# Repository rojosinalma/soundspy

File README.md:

<h1 align="center">soundspy</h1>
<p align="center">Real-time multi-node sound monitoring system for ESP32</p>

<p align="center">

</p>

ESP32 nodes with I2S MEMS microphones sample audio, meter it in six frequency bands plus an overall level, and publish the readings over MQTT. The dashboard discovers the nodes, shows live meters, spectrum and an hour of history per node, relays live audio from any node to the browser, and sends alerts (Telegram, Discord, ntfy, Pushover, email) when a configurable rule fires. One application is keeping an eye on how much of a rehearsal or a mix makes it through a shared wall; the same setup works for any room you want to listen to from elsewhere.

Hardware, firmware, dashboard, enclosure and design notes are documented in [`docs/`](docs/).

## Requirements

**Dashboard**
- Docker 24+ with Docker Compose v2 (or Python 3.12+ to run from source)
- An MQTT broker reachable by both the dashboard and the nodes, for example Eclipse Mosquitto 2.x

**Firmware**
- arduino-cli 1.x with the `esp32:esp32` core 3.3+
- The Esp32Base library for the current firmware (`firmware/`); the legacy firmware (`node_firmware/`) builds with PubSubClient, WebSockets and ArduinoJson from the library index

**Hardware (per node)**
- ESP32 development board (38-pin DevKit with 4 MB flash)
- ICS-43434 or INMP441 I2S MEMS microphone, optionally on the carrier PCB in `pcb/` — wiring in [docs/hardware.md](docs/hardware.md)

## Installation

```bash
git clone https://github.com/rojosinalma/soundspy.git && cd soundspy
cp .env.example .env     # broker address and credentials, dashboard port
docker compose up -d     # pulls ghcr.io/rojosinalma/soundspy:latest
```

The image runs as uid 1000; make sure `./data` is writable by that user (`chown -R 1000:1000 data`).

Then build and flash a node:

```bash
./scripts/init_arduino.sh                                     # ESP32 core + libraries (once)
ESP32_BASE_DIR=/path/to/Esp32Base ./scripts/build_firmware.sh
```

Flash `builds/soundspy_latest.bin` over USB the first time, then join the node's WiFi setup portal and enter your network and broker settings. Flashing, OTA updates and the legacy firmware are covered in [docs/firmware.md](docs/firmware.md).

## Usage

Open `http://<host>:8091`. A node appears on the dashboard as soon as it publishes; click its name to rename it, drag the threshold marker to set its alert level, and use the gain, sleep and live-audio controls on the card. Notification channels and alert rules live under **Settings**. The HTTP API (`GET /api/nodes`, `POST /api/control`, `GET /health`, …) is listed in [docs/dashboard.md](docs/dashboard.md).

## Development

```bash
# dashboard from source (templates reload; restart for Python changes)
cd dashboard && pip install -r requirements.txt && MQTT_HOST=<broker> DB_PATH=./soundspy.db python app.py

# checks
python -m py_compile dashboard/*.py && bash -n scripts/*.sh
./scripts/build_firmware.sh legacy
```

Layout, the Docker dev loop, enclosure rendering and the release flow are in [docs/development.md](docs/development.md); contribution rules in [CONTRIBUTING.md](CONTRIBUTING.md).

## License

[AGPL-3.0](LICENSE) — Copyright (C) 2026 rojosinalma

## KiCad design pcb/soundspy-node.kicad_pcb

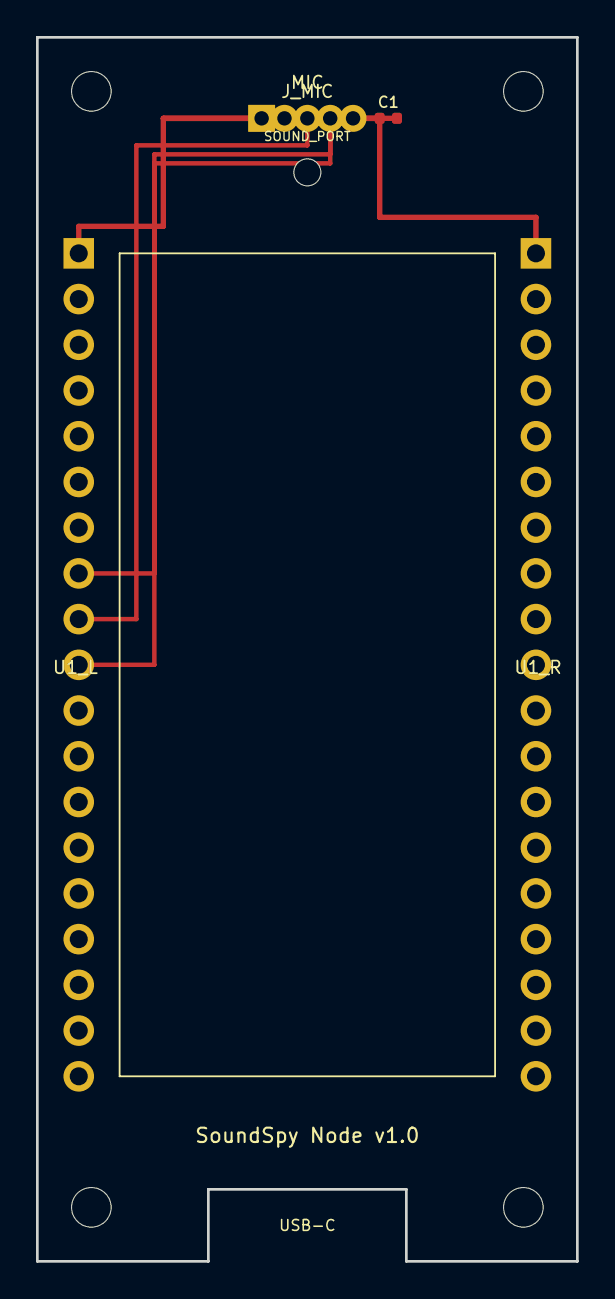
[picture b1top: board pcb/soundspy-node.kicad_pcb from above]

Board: 2 copper layers, 30.0 x 68.0 mm, 5 parts (0 on the bottom side), 5 nets.

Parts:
C1: 100nF; C_0402_1005Metric
J_MIC: ICS-43434; PinHeader_1x05_P1.27mm_Vertical
SOUND_PORT: MountingHole_1.5mm
U1_L: ESP32_L; PinHeader_1x19_P2.54mm_Vertical
U1_R: ESP32_R; PinHeader_1x19_P2.54mm_Vertical

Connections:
3V3: C1.1, J_MIC.1, U1_R.1
GND: C1.2, J_MIC.2, U1_L.1
I2S_SCK: J_MIC.5, U1_L.8
I2S_SD: J_MIC.4, U1_L.10
I2S_WS: J_MIC.3, U1_L.9

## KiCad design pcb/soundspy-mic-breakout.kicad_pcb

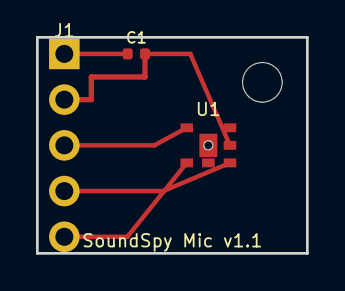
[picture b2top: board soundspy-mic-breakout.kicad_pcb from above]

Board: 2 copper layers, 15.0 x 12.0 mm, 3 parts (0 on the bottom side), 5 nets.

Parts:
C1: 100nF; C_0402_1005Metric
J1: ESP32; PinHeader_1x05_P2.54mm_Vertical
U1: ICS-43434; LGA-8_3.5x2.65mm_P1.27mm

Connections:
3V3: C1.1, J1.1, U1.5
GND: C1.2, J1.2, U1.3, U1.4, U1.7
I2S_SCK: J1.5, U1.2
I2S_SD: J1.4, U1.6
I2S_WS: J1.3, U1.1

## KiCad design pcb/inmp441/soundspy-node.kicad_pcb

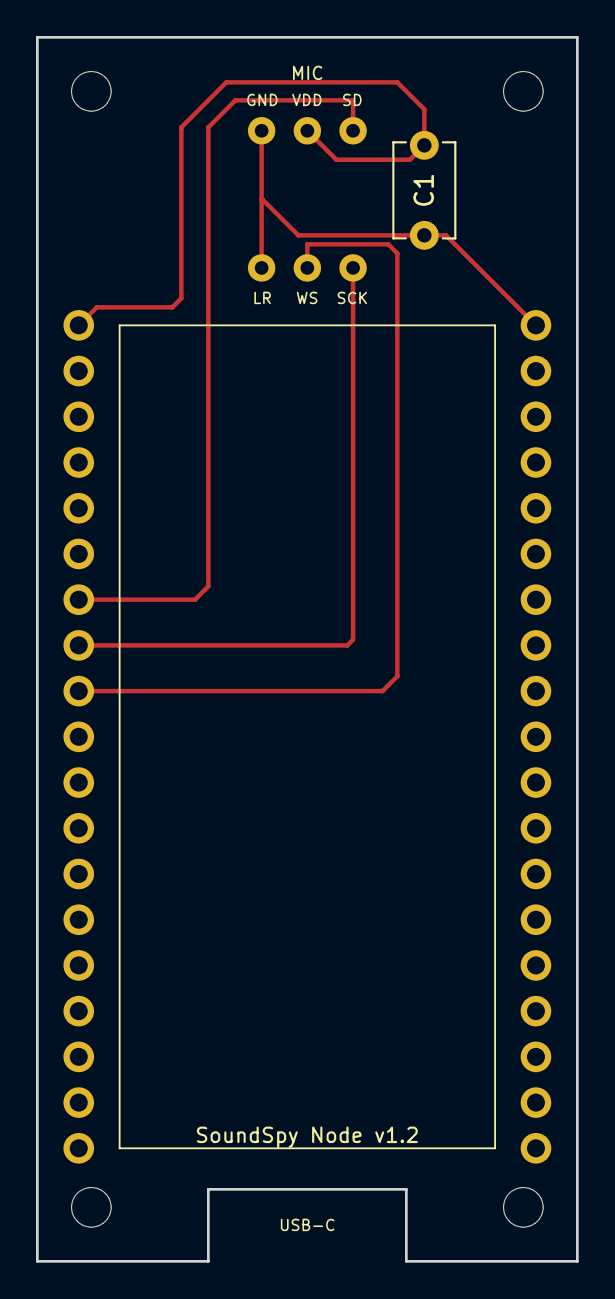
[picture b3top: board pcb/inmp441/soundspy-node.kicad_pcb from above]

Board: 2 copper layers, 30.0 x 68.0 mm, 4 parts (0 on the bottom side), 5 nets.

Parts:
C1: C_Disc_D5.1mm_W3.2mm_P5.00mm
MIC: INMP441; PinHeader_2x03_P2.54mm_Vertical
U1_L: ESP32_L; PinHeader_1x19_P2.54mm_Vertical
U1_R: ESP32_R; PinHeader_1x19_P2.54mm_Vertical

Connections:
3V3: C1.2, MIC.2, U1_L.1
GND: C1.1, MIC.1, MIC.4, U1_R.1
I2S_SCK: MIC.6, U1_L.8
I2S_SD: MIC.3, U1_L.7
I2S_WS: MIC.5, U1_L.9

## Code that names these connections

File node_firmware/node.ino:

/*
  Bass Monitor Node — ESP32 + I2S mic (INMP441 or ICS-43434)

  Reads audio via I2S, computes:
    - overall_dbfs : RMS level of the full captured band (relative dBFS, not calibrated SPL)
    - bass_dbfs    : RMS level after a ~150Hz lowpass (isolates the bass/low-freq band)
  and publishes both over MQTT once per second.

  Wiring (same for INMP441 and ICS-43434 — pin-compatible):
    VDD  -> 3.3V
    GND  -> GND
    SD   -> GPIO32   (I2S data in)
    WS   -> GPIO25   (I2S word select / LR clock)
    SCK  -> GPIO33   (I2S bit clock)
    L/R  -> GND      (selects left channel; tie to 3.3V for right if ever needed)

  IMPORTANT: set NODE_ID, WIFI_SSID, WIFI_PASS, MQTT_HOST below per-device
  before flashing each of the 3 boards.
*/

#include <WiFi.h>
#include <PubSubClient.h>
#include <driver/i2s.h>
#include <math.h>

// ---------- PER-NODE CONFIG (edit NODE_ID for each of the 3 boards) ----------
const char* NODE_ID    = "wall1";              // wall1, wall2, wall3
const char* WIFI_SSID  = "rojo_IoT";
const char* WIFI_PASS  = "19032000";
const char* MQTT_HOST  = "10.10.10.20";        // silver server IP
const int   MQTT_PORT  = 1883;
// -----------------------------------------------------------------------------

// I2S pins (identical across all 3 nodes)
#define I2S_WS   25
#define I2S_SD   32
#define I2S_SCK  33
#define I2S_PORT I2S_NUM_0

// Audio config
#define SAMPLE_RATE     44100
#define SAMPLES_PER_READ 1024
#define PUBLISH_INTERVAL_MS 1000

int32_t i2s_read_buf[SAMPLES_PER_READ];

WiFiClient espClient;
PubSubClient mqtt(espClient);

// --- simple 2nd-order Butterworth lowpass biquad, cascaded x2 (~150Hz @ 44.1kHz) ---
// Coefficients precomputed for fc=150Hz, fs=44100Hz, Q=0.707
struct Biquad {
  float b0, b1, b2, a1, a2;
  float z1 = 0, z2 = 0;
  float process(float in) {
    float out = b0 * in + z1;
    z1 = b1 * in + z2 - a1 * out;
    z2 = b2 * in - a2 * out;
    return out;
  }
};

Biquad lp1, lp2;

void configureLowpass() {
  // fc=150Hz, fs=44100Hz Butterworth LPF coefficients (Q=0.7071)
  float b0 = 0.0000453f, b1 = 0.0000906f, b2 = 0.0000453f;
  float a1 = -1.9772f,  a2 = 0.9776f;
  lp1 = {b0, b1, b2, a1, a2};
  lp2 = {b0, b1, b2, a1, a2};
}

// accumulators for 1-second aggregation
double sumSquaresOverall = 0;
double sumSquaresBass = 0;
uint32_t sampleCount = 0;
unsigned long lastPublish = 0;

void setupI2S() {
  i2s_config_t i2s_config = {
    .mode = (i2s_mode_t)(I2S_MODE_MASTER | I2S_MODE_RX),
    .sample_rate = SAMPLE_RATE,
    .bits_per_sample = I2S_BITS_PER_SAMPLE_32BIT,
    .channel_format = I2S_CHANNEL_FMT_ONLY_LEFT,
    .communication_format = I2S_COMM_FORMAT_STAND_I2S,
    .intr_alloc_flags = ESP_INTR_FLAG_LEVEL1,
    .dma_buf_count = 8,
    .dma_buf_len = SAMPLES_PER_READ,
    .use_apll = false,
    .tx_desc_auto_clear = false,
    .fixed_mclk = 0
  };

  i2s_pin_config_t pin_config = {
    .bck_io_num = I2S_SCK,
    .ws_io_num = I2S_WS,
    .data_out_num = I2S_PIN_NO_CHANGE,
    .data_in_num = I2S_SD
  };

  i2s_driver_install(I2S_PORT, &i2s_config, 0, NULL);
  i2s_set_pin(I2S_PORT, &pin_config);
}

void connectWiFi() {
  WiFi.begin(WIFI_SSID, WIFI_PASS);
  Serial.print("Connecting to WiFi");
  while (WiFi.status() != WL_CONNECTED) {
    delay(500);
    Serial.print(".");
  }
  Serial.println(" connected");
}

void connectMQTT() {
  mqtt.setServer(MQTT_HOST, MQTT_PORT);
  while (!mqtt.connected()) {
    Serial.print("Connecting to MQTT...");
    String clientId = String("esp32-") + NODE_ID;
    if (mqtt.connect(clientId.c_str())) {
      Serial.println(" connected");
    } else {
      Serial.print("failed, rc=");
      Serial.print(mqtt.state());
      Serial.println(" retrying in 2s");
      delay(2000);
    }
  }
}

void setup() {
  Serial.begin(115200);
  configureLowpass();
  setupI2S();
  connectWiFi();
  connectMQTT();
  lastPublish = millis();
}

void loop() {
  if (!mqtt.connected()) connectMQTT();
  mqtt.loop();

  size_t bytesRead = 0;
  i2s_read(I2S_PORT, i2s_read_buf, sizeof(i2s_read_buf), &bytesRead, portMAX_DELAY);
  int samplesRead = bytesRead / sizeof(int32_t);

  for (int i = 0; i < samplesRead; i++) {
    // INMP441/ICS-43434 output 24-bit data left-justified in the 32-bit word
    int32_t raw = i2s_read_buf[i] >> 8;          // shift down to 24-bit signed value
    float sample = (float)raw / 8388608.0f;      // normalize to [-1.0, 1.0] (2^23)

    sumSquaresOverall += (double)(sample * sample);

    float bass = lp1.process(sample);
    bass = lp2.process(bass);
    sumSquaresBass += (double)(bass * bass);

    sampleCount++;
  }

  if (millis() - lastPublish >= PUBLISH_INTERVAL_MS && sampleCount > 0) {
    float rmsOverall = sqrt(sumSquaresOverall / sampleCount);
    float rmsBass = sqrt(sumSquaresBass / sampleCount);

    // relative dBFS (0 dBFS = full-scale digital signal). NOT calibrated SPL —
    // calibrate empirically by noting readings during known-loud reference events.
    float dbfsOverall = 20.0f * log10f(rmsOverall + 1e-9f);
    float dbfsBass = 20.0f * log10f(rmsBass + 1e-9f);

    char payload[160];
    snprintf(payload, sizeof(payload),
      "{\"node\":\"%s\",\"overall_dbfs\":%.1f,\"bass_dbfs\":%.1f}",
      NODE_ID, dbfsOverall, dbfsBass);

    String topic = String("bassmonitor/") + NODE_ID + "/data";
    mqtt.publish(topic.c_str(), payload);

    Serial.println(payload);

    sumSquaresOverall = 0;
    sumSquaresBass = 0;
    sampleCount = 0;
    lastPublish = millis();
  }
}
